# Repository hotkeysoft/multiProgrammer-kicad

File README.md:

# Multi-Programmer With Serial / SPI Programming
Rev A August 2019

Features
============
- Sockets for direct programming:
	- ATMEGA328P TQFP 32 (via adapter)
	- ATMEGA328P DIP 28 pins
	- ATTINY44/84
	- ATTINY45/85
- Headers for in-circuit programming:
	- Serial Header:
		- 5 pins 2.54mm
	- SPI Headers (too many):
		- 2x3 pins 2.54mm (99% of use)
		- 2x3 pins 1.27mm
		- 1x6 pins 1.25mm (micro-JST)
		- Tag-Connect (mostly useless, since there are no two-ended 
		  Tag-Connect cables. Will be removed in future revisions)
- Two programming modes:
	- Serial passtrough
		- Useful to programm chips with Arduino bootloader, or for any USB<->Serial adapter needs
	- ICSP Programming
		- Compatible with _Arduino as ISP_ programmer in Arduino interface
	- Toggle Serial/ICSP mode with pushbutton switch
- USB-B port (could be a downside but I am fond of them: they are sturdy)

Notes
============
- Socketed chips:
	- _ATmega328P_ running _ArduinoISP_
	- _555_ Used for Mode switch debouncing (old school)
	- _PALCE16V8_ for mode switching logic (LEDs, pin routing) [source](PLD/TTLSW.PDS) 
- Optional crystal socket, not needed for new chips (internal clock is used)
 	- Required for serial programming if the target is set to use an external crystal
	  (Need to confirm if needed in SPI mode)
- Boots in serial mode, be sure to switch mode to use SPI mode
- Reset button resets the target chip (in both modes) and the _Arduino as ISP_ software
- Don't put more than one target chip at a time (undefined behavior, no protection, might destroy the universe)

Images
============

|Render                                                | Real PCB                                       |
|------------------------------------------------------|------------------------------------------------|
|||
|   |   |

### Schematics (pdf)
- [Complete schematics](./img/schema.pdf)

### PCB Images (svg)
- [Top](./img/pcb-front.svg)
- [Bottom](./img/pcb-back.svg)

Future
============
- Try to combine 555 and programmable logic on Arduino
- Remove useless connectors
- Save mode in EEPROM so it is remembered on next power-up
- LEDs are too bright

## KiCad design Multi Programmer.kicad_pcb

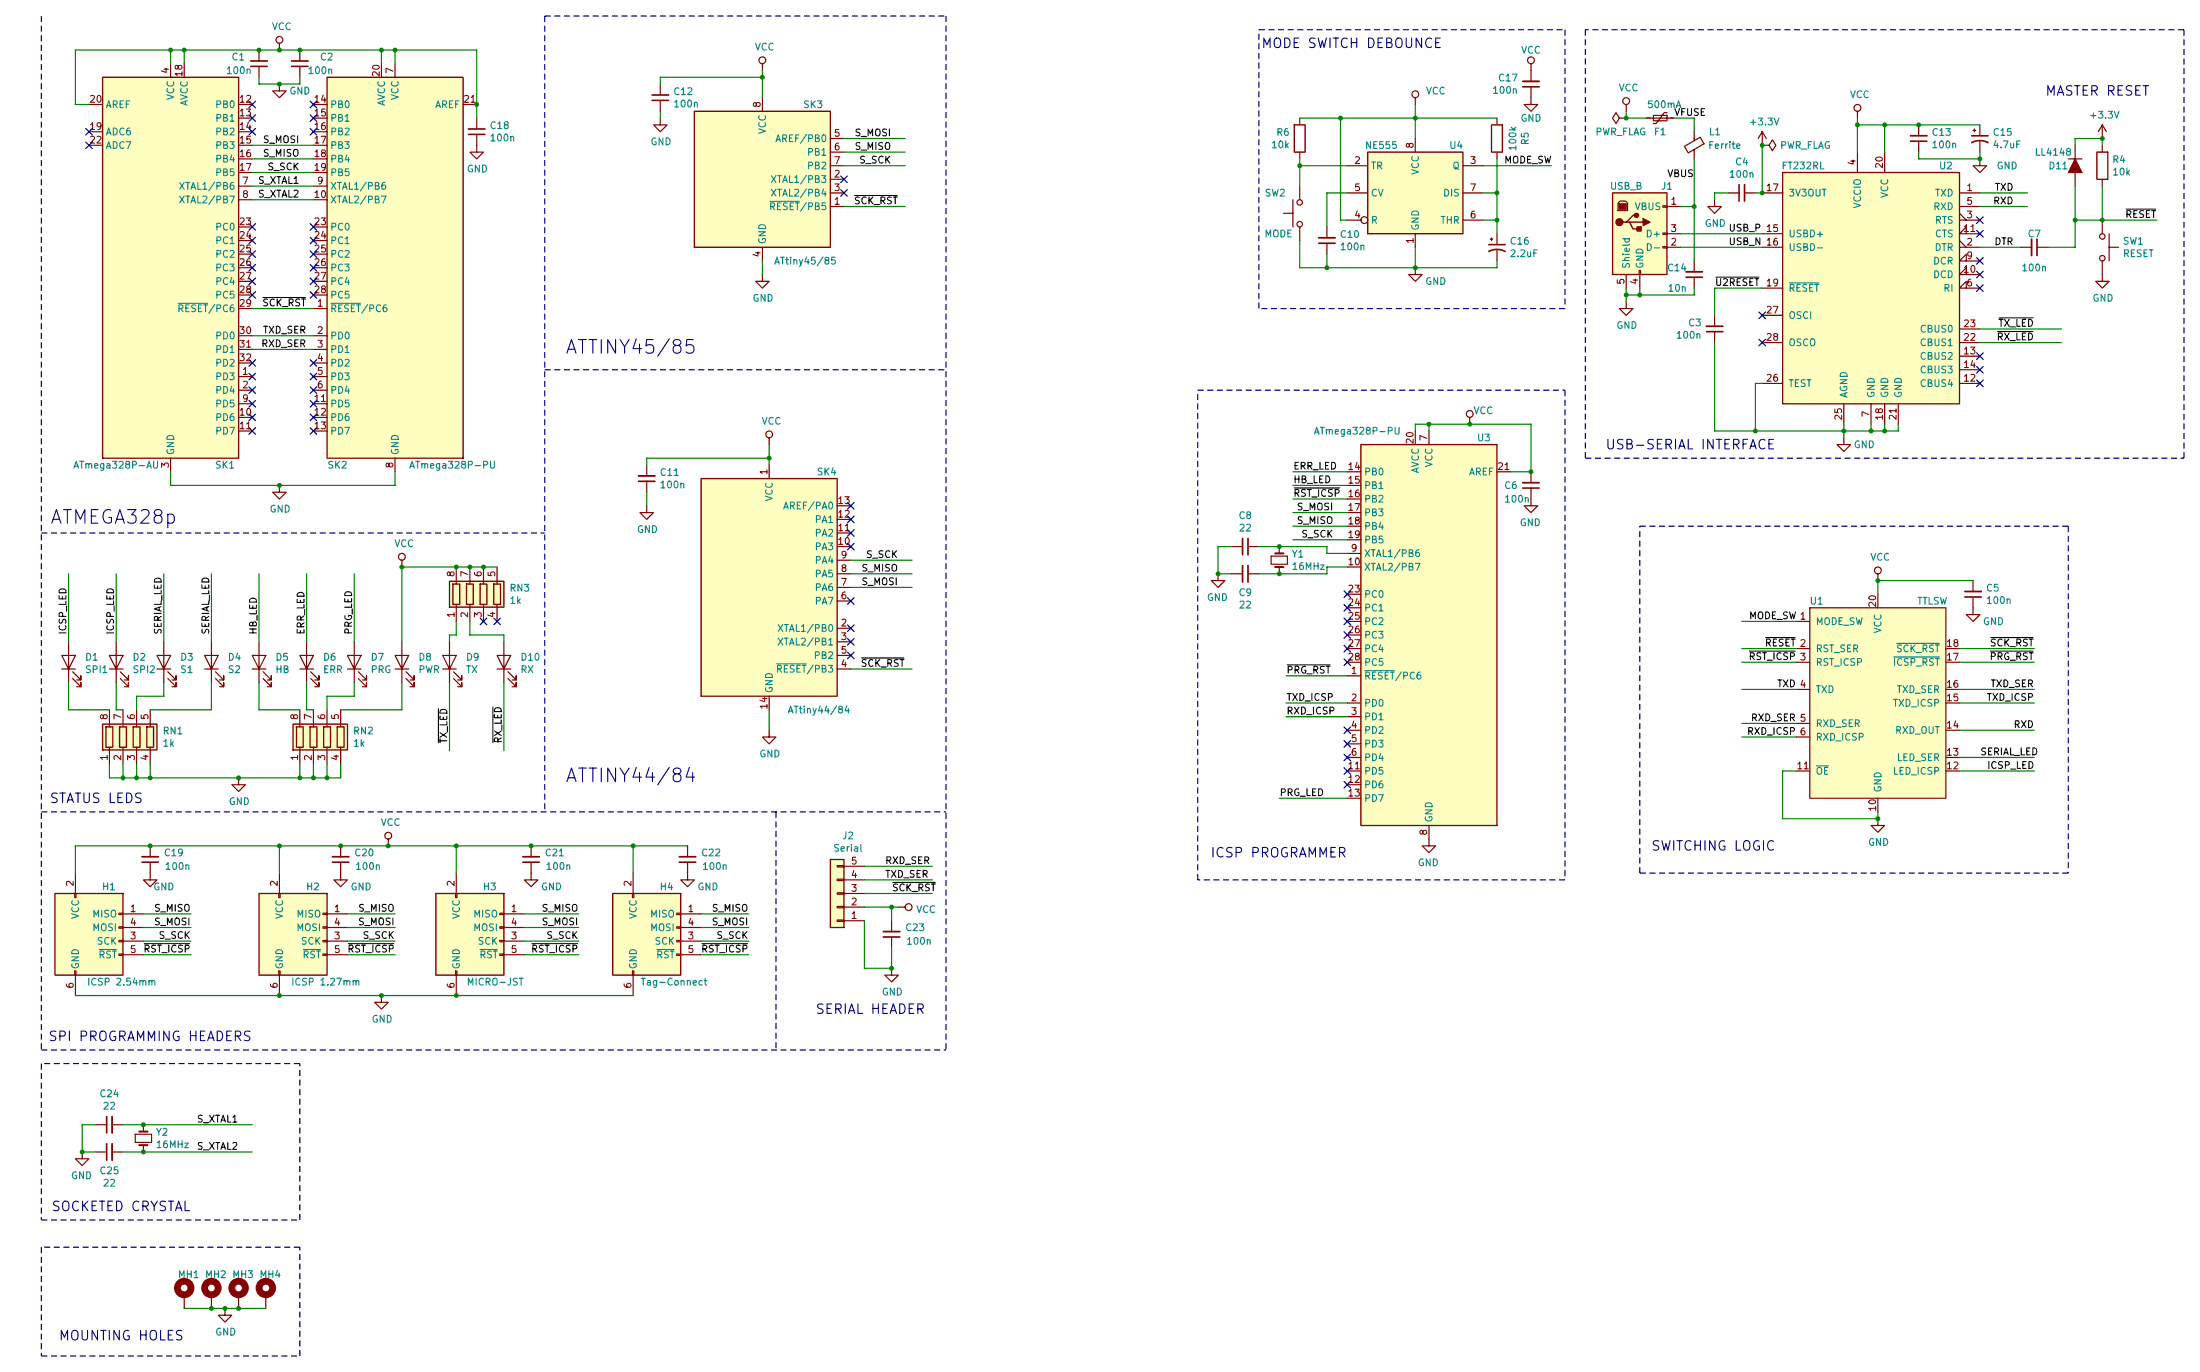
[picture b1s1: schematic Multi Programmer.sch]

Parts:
C1, C2, C3, C4, C5, C6, C7, C10, C11, C12, C13, C17, C18, C19, C20, C21, C22, C23: 100n; C_0805_2012Metric_Pad1.15x1.40mm_HandSolder
C8, C9, C24, C25: 22; C_0805_2012Metric_Pad1.15x1.40mm_HandSolder
C14: 10n; C_0805_2012Metric_Pad1.15x1.40mm_HandSolder
C15: 4.7uF; CP_Radial_D4.0mm_P2.00mm
C16: 2.2uF; CP_Radial_D4.0mm_P2.00mm
D1: SPI1; LED_1206_3216Metric_Pad1.42x1.75mm_HandSolder
D2: SPI2; LED_1206_3216Metric_Pad1.42x1.75mm_HandSolder
D3: S1; LED_1206_3216Metric_Pad1.42x1.75mm_HandSolder
D4: S2; LED_1206_3216Metric_Pad1.42x1.75mm_HandSolder
D5: HB; LED_1206_3216Metric_Pad1.42x1.75mm_HandSolder
D6: ERR; LED_1206_3216Metric_Pad1.42x1.75mm_HandSolder
D7: PRG; LED_1206_3216Metric_Pad1.42x1.75mm_HandSolder
D8: PWR; LED_1206_3216Metric_Pad1.42x1.75mm_HandSolder
D9: TX; LED_1206_3216Metric_Pad1.42x1.75mm_HandSolder
D10: RX; LED_1206_3216Metric_Pad1.42x1.75mm_HandSolder
D11: LL4148; SOD80
F1: 500mA; Fuse_1812_4532Metric_Pad1.30x3.40mm_HandSolder
H1: ICSP 2.54mm; PinHeader_2x03_P2.54mm_Vertical
H2: ICSP 1.27mm; PinHeader_2x03_P1.27mm_Vertical
H3: MICRO-JST; Hirose_DF13-06P-1.25DSA_1x06_P1.25mm_Vertical
H4: Tag-Connect; Tag-Connect_TC2030-IDC-NL_2x03_P1.27mm_Vertical
J1: USB_B; USB_B_OST_USB-B1HSxx_Horizontal
J2: Serial; PinSocket_1x05_P2.54mm_Vertical
L1: Ferrite; L_0805_2012Metric_Pad1.15x1.40mm_HandSolder
MH1, MH2, MH3, MH4: MountingHole; TestPoint_Plated_Hole_D3.0mm
R4, R6: 10k; R_0805_2012Metric_Pad1.15x1.40mm_HandSolder
R5: 100k; R_0805_2012Metric_Pad1.15x1.40mm_HandSolder
RN1, RN2, RN3: 1k; R_Array_Convex_4x1206
SK1: ATmega328P-AU; DIP-32_W15.24mm_Socket
SK2: ATmega328P-PU; DIP-28_Zif_Multi
SK3: ATtiny45/85; DIP-8_W7.62mm
SK4: ATtiny44/84; DIP-14_W7.62mm
SW1: RESET; Switch_Tactile_SMD_6x6mm_PTS645
SW2: MODE; Switch_Tactile_SMD_6x6mm_PTS645
U1: TTLSW; DIP-20_W7.62mm_Socket
U2: FT232RL; SSOP-28_5.3x10.2mm_P0.65mm
U3: ATmega328P-PU; DIP-28_W7.62mm_Socket
U4: NE555; DIP-8_W7.62mm_Socket
Y1, Y2: 16MHz; Crystal_HC18-U_Vertical

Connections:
+3V3: C4.2, D11.1 (K), R4.2, U2.17 (3V3OUT)
/DTR: C7.2, U2.2 (DTR)
/ERR_LED: D6.2 (A), U3.14 (PB0)
/HB_LED: D5.2 (A), U3.15 (PB1)
/ICSP_LED: D1.2 (A), D2.2 (A), U1.12 (LED_ICSP)
/MODE_SW: U1.1 (MODE_SW), U4.3 (Q)
/PRG_LED: D7.2 (A), U3.13 (PD7)
/RXD: U1.14 (RXD_OUT), U2.5 (RXD)
/RXD_ICSP: U1.6 (RXD_ICSP), U3.3 (PD1)
/RXD_SER: J2.5, SK1.31 (PD1), SK2.3 (PD1), U1.5 (RXD_SER)
/SERIAL_LED: D3.2 (A), D4.2 (A), U1.13 (LED_SER)
/S_MISO: H1.1 (MISO), H2.1 (MISO), H3.1 (MISO), H4.1 (MISO), SK1.16 (PB4), SK2.18 (PB4), SK3.6 (PB1), SK4.8 (PA5), U3.18 (PB4)
/S_MOSI: H1.4 (MOSI), H2.4 (MOSI), H3.4 (MOSI), H4.4 (MOSI), SK1.15 (PB3), SK2.17 (PB3), SK3.5 (AREF/PB0), SK4.7 (PA6), U3.17 (PB3)
/S_SCK: H1.3 (SCK), H2.3 (SCK), H3.3 (SCK), H4.3 (SCK), SK1.17 (PB5), SK2.19 (PB5), SK3.7 (PB2), SK4.9 (PA4), U3.19 (PB5)
/S_XTAL1: C24.2, SK1.7 (XTAL1/PB6), SK2.9 (XTAL1/PB6), Y2.1
/S_XTAL2: C25.2, SK1.8 (XTAL2/PB7), SK2.10 (XTAL2/PB7), Y2.2
/TXD: U1.4 (TXD), U2.1 (TXD)
/TXD_ICSP: U1.15 (TXD_ICSP), U3.2 (PD0)
/TXD_SER: J2.4, SK1.30 (PD0), SK2.2 (PD0), U1.16 (TXD_SER)
/USB_N: J1.2 (D-), U2.16 (USBD-)
/USB_P: J1.3 (D+), U2.15 (USBD+)
/VBUS: C14.2, J1.1 (VBUS), L1.2
/VFUSE: F1.1, L1.1
/~PRG_RST: U1.17 (~ICSP_RST), U3.1 (~RESET~/PC6)
/~RESET: C7.1, D11.2 (A), R4.1, SW1.1, U1.2 (RST_SER)
/~RST_ICSP: H1.5 (~RST), H2.5 (~RST), H3.5 (~RST), H4.5 (~RST), U1.3 (RST_ICSP), U3.16 (PB2)
/~RX_LED: D10.1 (K), U2.22 (CBUS1)
/~SCK_RST: J2.3, SK1.29 (~RESET~/PC6), SK2.1 (~RESET~/PC6), SK3.1 (~RESET~/PB5), SK4.4 (~RESET~/PB3), U1.18 (~SCK_RST)
/~TX_LED: D9.1 (K), U2.23 (CBUS0)
/~U2RESET: C3.2, U2.19 (~RESET~)
GND: C1.1, C2.1, C3.1, C4.1, C5.1, C6.1, C8.1, C9.1, C10.1, C11.1, C12.1, C13.1, C14.1, C15.2, C16.2, C17.1, C18.1, C19.1, C20.1, C21.1, C22.1, C23.1, C24.1, C25.1, H1.6 (GND), H2.6 (GND), H3.6 (GND), H4.6 (GND), J1.4 (GND), J1.5 (Shield), J2.1, MH1.1, MH2.1, MH3.1, MH4.1, RN1.1 (R1.1), RN1.2 (R2.1), RN1.3 (R3.1), RN1.4 (R4.1), RN2.1 (R1.1), RN2.2 (R2.1), RN2.3 (R3.1), RN2.4 (R4.1), SK1.3 (GND), SK1.5 (GND), SK1.21 (GND), SK2.8 (GND), SK2.22 (GND), SK3.4 (GND), SK4.14 (GND), SW1.2, SW2.2, U1.10 (GND), U1.11 (~OE), U2.7 (GND), U2.18 (GND), U2.21 (GND), U2.25 (AGND), U2.26 (TEST), U3.8 (GND), U3.22 (GND), U4.1 (GND)
unnamed: C8.2, U3.9 (XTAL1/PB6), Y1.1
unnamed: C9.2, U3.10 (XTAL2/PB7), Y1.2
unnamed: C10.2, U4.5 (CV)
unnamed: C16.1, R5.1, U4.6 (THR), U4.7 (DIS)
unnamed: D1.1 (K), RN1.8 (R1.2)
unnamed: D2.1 (K), RN1.7 (R2.2)
unnamed: D3.1 (K), RN1.6 (R3.2)
unnamed: D4.1 (K), RN1.5 (R4.2)
unnamed: D5.1 (K), RN2.8 (R1.2)
unnamed: D6.1 (K), RN2.7 (R2.2)
unnamed: D7.1 (K), RN2.6 (R3.2)
unnamed: D8.1 (K), RN2.5 (R4.2)
unnamed: D9.2 (A), RN3.1 (R1.1)
unnamed: D10.2 (A), RN3.2 (R2.1)
unnamed: R6.1, SW2.1, U4.2 (TR)
VCC: C1.2, C2.2, C5.2, C6.2, C11.2, C12.2, C13.2, C15.1, C17.2, C18.2, C19.2, C20.2, C21.2, C22.2, C23.2, D8.2 (A), F1.2, H1.2 (VCC), H2.2 (VCC), H3.2 (VCC), H4.2 (VCC), J2.2, R5.2, R6.2, RN3.5 (R4.2), RN3.6 (R3.2), RN3.7 (R2.2), RN3.8 (R1.2), SK1.4 (VCC), SK1.6 (VCC), SK1.18 (AVCC), SK1.20 (AREF), SK2.7 (VCC), SK2.20 (AVCC), SK2.21 (AREF), SK3.8 (VCC), SK4.1 (VCC), U1.20 (VCC), U2.4 (VCCIO), U2.20 (VCC), U3.7 (VCC), U3.20 (AVCC), U3.21 (AREF), U4.4 (R), U4.8 (VCC)

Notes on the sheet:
SPI PROGRAMMING HEADERS
STATUS LEDS
SERIAL HEADER
MODE SWITCH DEBOUNCE
USB-SERIAL INTERFACE
MASTER RESET
ICSP PROGRAMMER
SWITCHING LOGIC
MOUNTING HOLES
ATMEGA328p
ATTINY45/85
ATTINY44/84
SOCKETED CRYSTAL

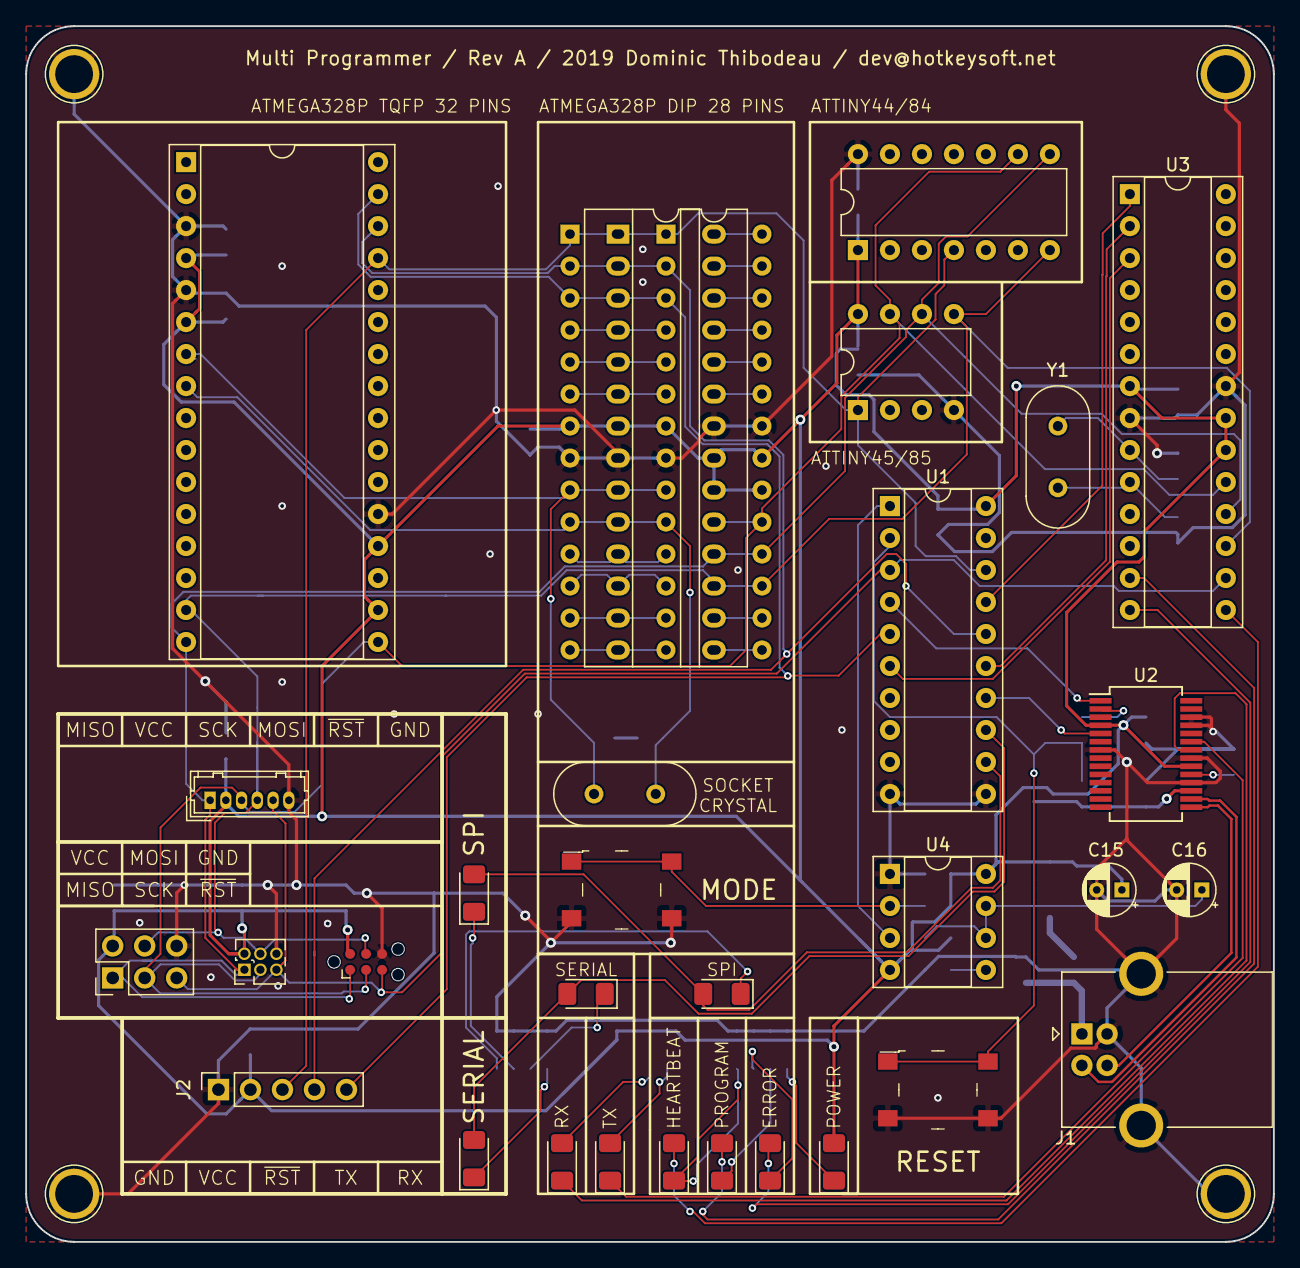
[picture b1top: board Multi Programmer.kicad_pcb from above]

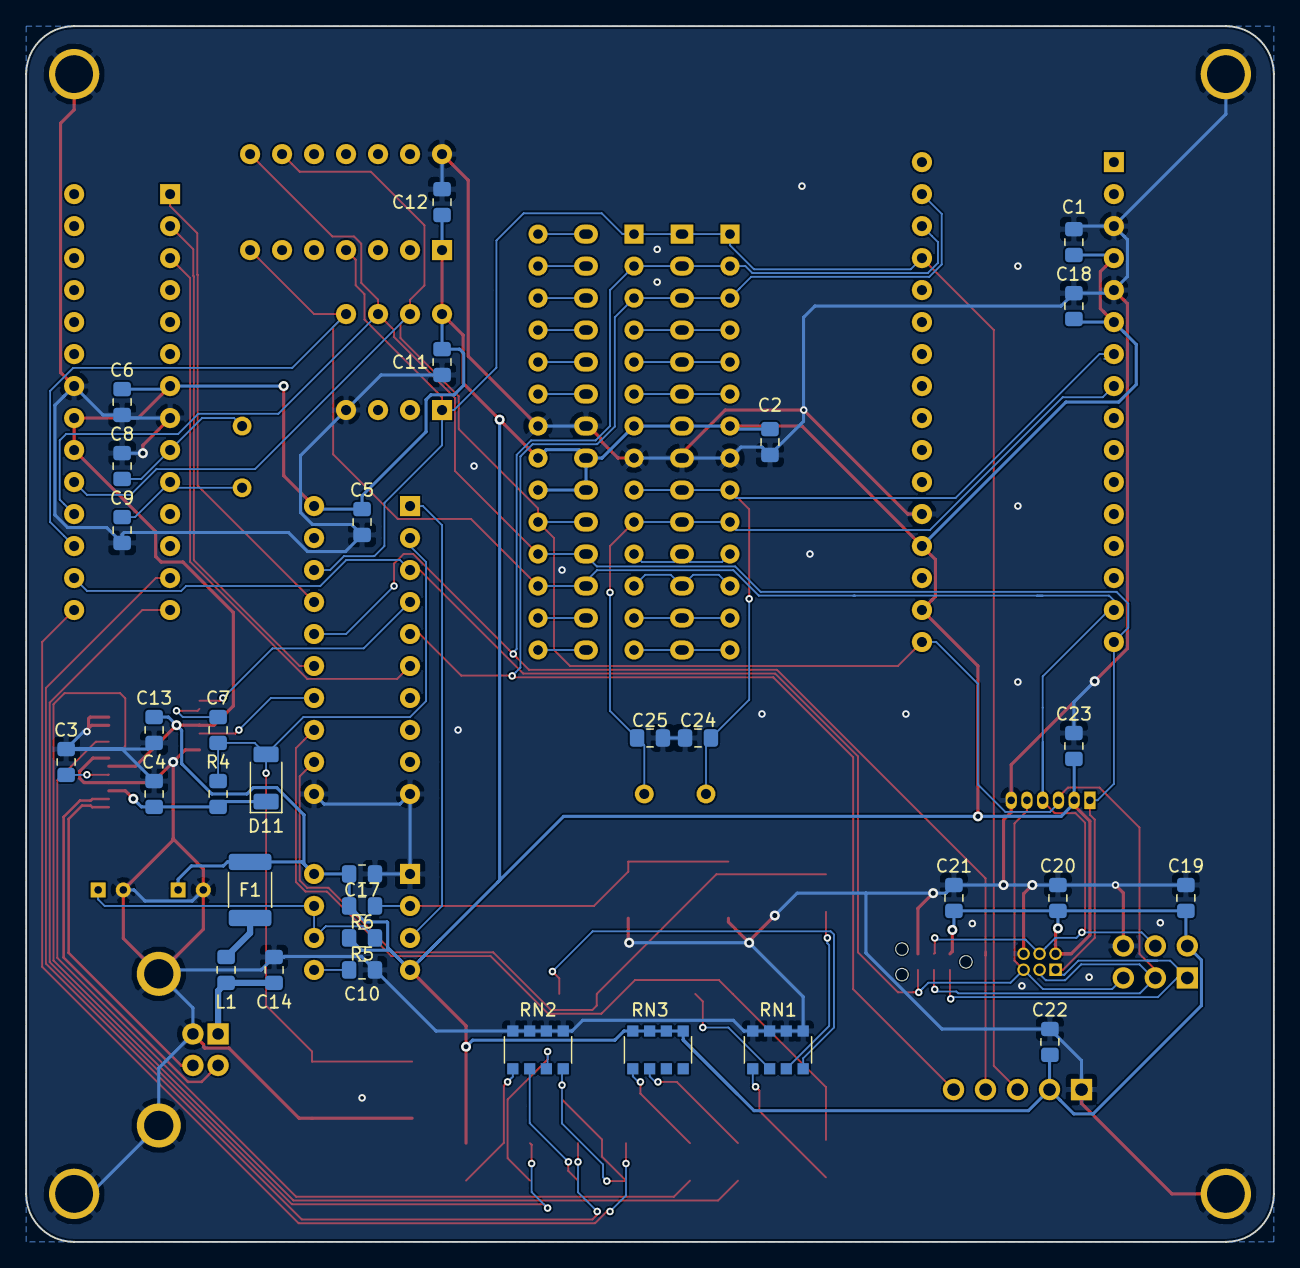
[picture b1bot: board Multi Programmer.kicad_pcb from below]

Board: 2 copper layers, 99.1 x 96.5 mm, 66 parts (32 on the bottom side), 47 nets.

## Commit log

2019-08-14 Initial import
2019-08-14 Added sockets for attiny, move sockets to separate page
2019-08-14 Round edges
2019-08-17 Repositioned crystal
2019-08-23 Add PCB Fabrication zip files
2019-10-21 path
2020-07-03 Removed cache file
2020-07-03 Cleanup, added images
2020-07-03 Renamed project
2020-07-03 Added images and readme
2020-07-03 Create LICENSE
2020-07-03 Fixed names
